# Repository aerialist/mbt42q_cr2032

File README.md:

# MDBT42Q BLE module breakout board

This is a breakout board for MDBT42Q module, a nRF52 based BLE.
https://www.seeedstudio.com/MDBT42Q-nRF52832-based-BLE-module-p-2736.html
http://www.raytac.com/product/ins.php?index_id=31

Schematics is largely copied from and inspired by Adafruit Feather nRF52 Bluefruit LE
https://www.adafruit.com/product/3406
https://learn.adafruit.com/bluefruit-nrf52-feather-learning-guide/introduction

and Redbear BLE Nano v2
https://redbear.cc/product/ble/ble-nano-2-soldered.html
https://github.com/redbear/nRF5x/tree/master/nRF52832

so that Arduino BSP developed by Adafruit or Redbear could be used as well as SDK from Nordic.
(Personally I'd recommend to go with Adafruit now that Redbear joined Particle)

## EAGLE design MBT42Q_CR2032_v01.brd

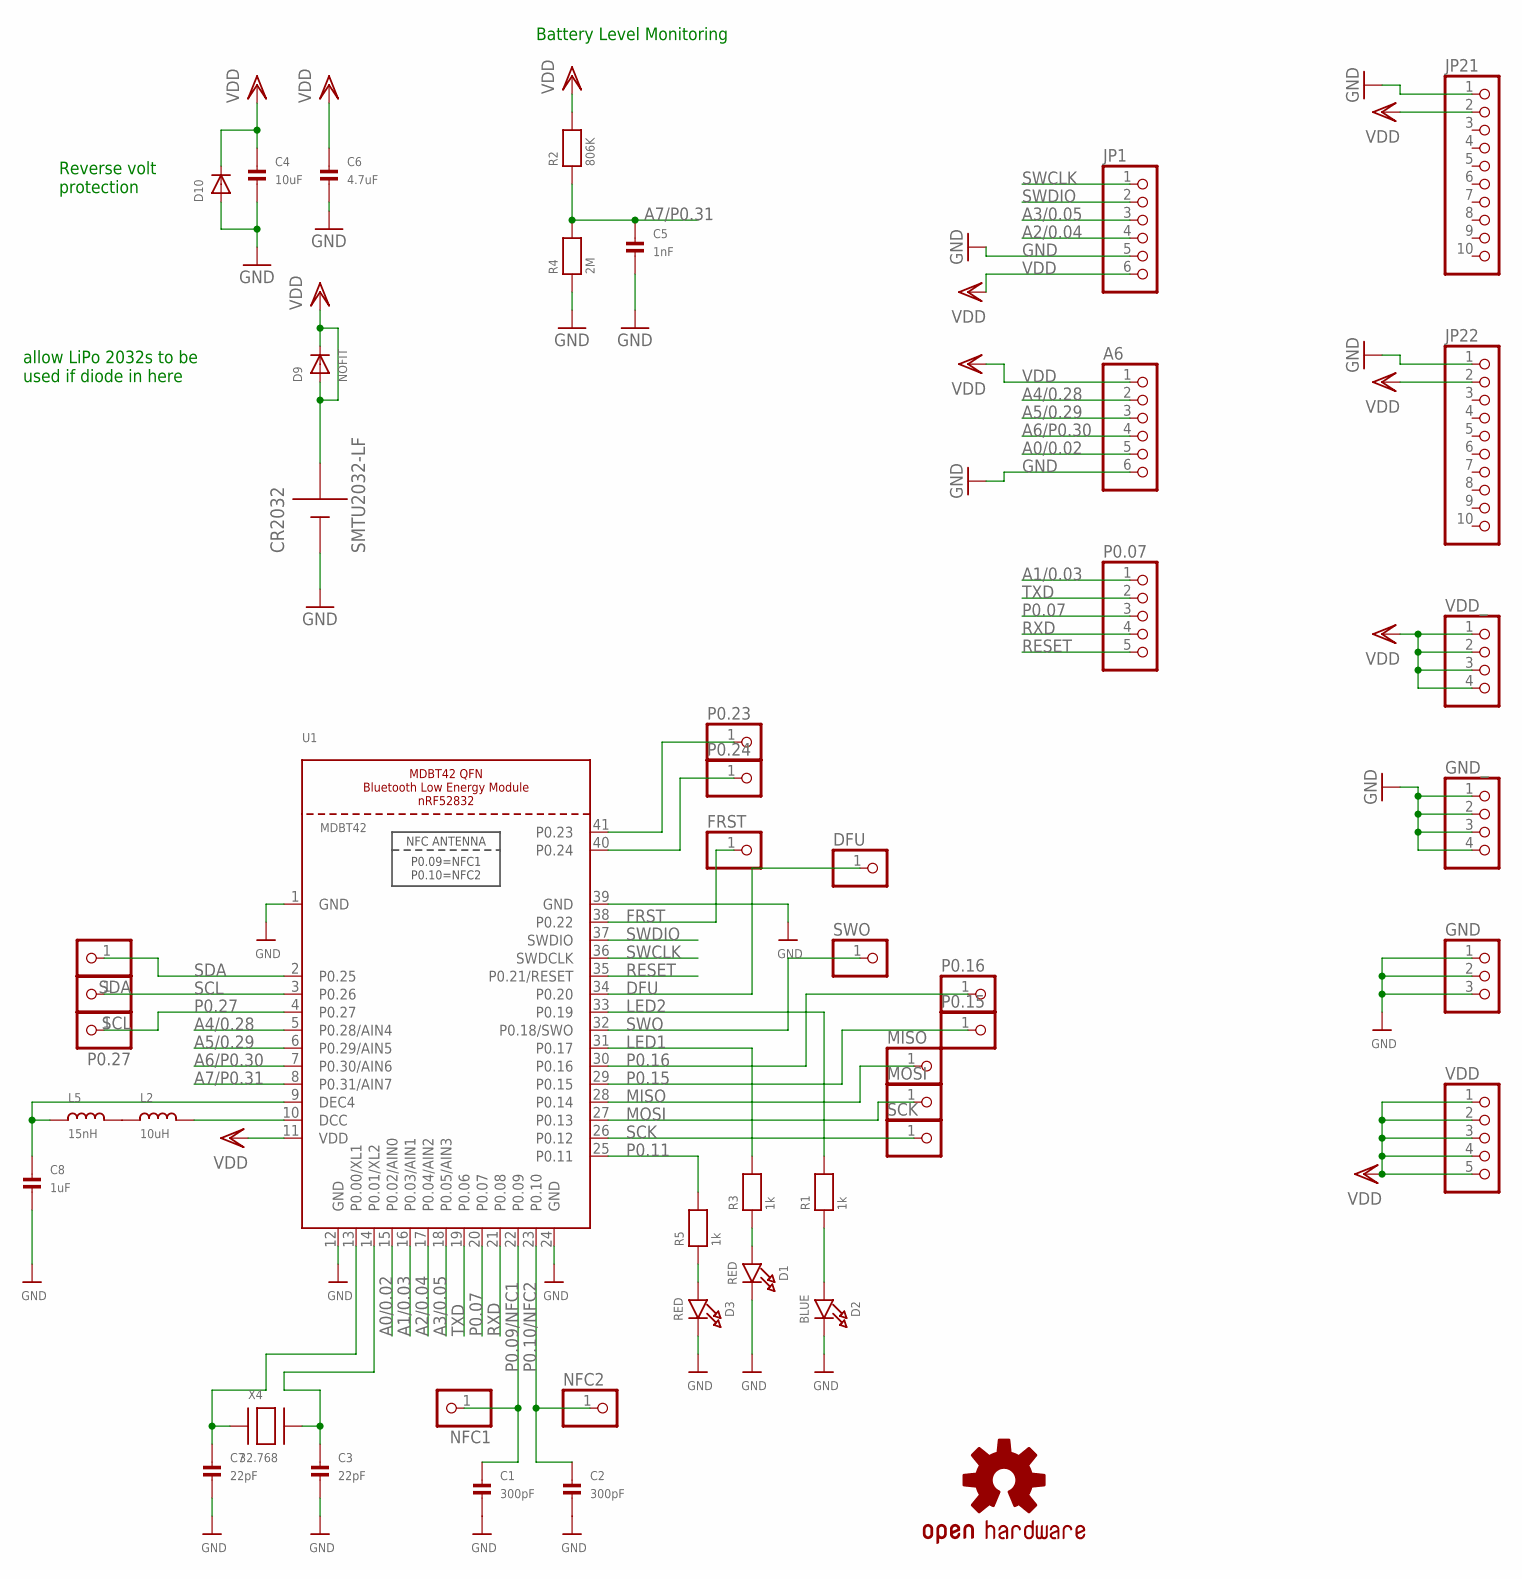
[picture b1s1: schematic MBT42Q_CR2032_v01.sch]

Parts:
A6: HEADER-1X6ROUND; 1X06_ROUND
C1, C2: 300pF; 0805
C3, C7: 22pF; 0805
C4: 10uF; 0805
C5: 1nF; 0805
C6: 4.7uF; 0805
C8: 1uF; 0805
CR2032: SMTU2032-LF
D1, D3: RED; CHIPLED_0805_NOOUTLINE
D2: BLUE; CHIPLED_0805_NOOUTLINE
D9: NOFIT; SOD-523
D10: DIODESOD-523; SOD-523
DFU: HEADER-1X1ROUND; 1X01_ROUND
FRST: HEADER-1X1ROUND; 1X01_ROUND
GND: HEADER-1X3ROUND; 1X03_ROUND
GND_: HEADER-1X4ROUND; 1X04_ROUND
JP1: HEADER-1X6ROUND; 1X06_ROUND
JP21, JP22: HEADER-1X10ROUND; 1X10_ROUND
L2: 10uH; _0805
L5: 15nH; _0805
LOGO1: OSHW-LOGOS; OSHW-LOGO-S
MISO: HEADER-1X1ROUND; 1X01_ROUND
MOSI: HEADER-1X1ROUND; 1X01_ROUND
NFC1, NFC2: HEADER-1X1ROUND; 1X01_ROUND
P0.07: HEADER-1X5ROUND; 1X05_ROUND
P0.15, P0.16, P0.23, P0.24, P0.27: HEADER-1X1ROUND; 1X01_ROUND
R1, R3, R5: 1k; 0805
R2: 806K; 0805
R4: 2M; 0805
SCK: HEADER-1X1ROUND; 1X01_ROUND
SCL: HEADER-1X1ROUND; 1X01_ROUND
SDA: HEADER-1X1ROUND; 1X01_ROUND
SWO: HEADER-1X1ROUND; 1X01_ROUND
U1: MDBT42; BLE_MODULE_RAYTAC_MDBT42
VDD: HEADER-1X5ROUND; 1X05_ROUND
VDD_: HEADER-1X4ROUND; 1X04_ROUND
X4: 32.768; XTAL3215

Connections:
A0/0.02: A6.5, U1.15 (P0.02/AIN0)
A1/0.03: P0.07.1, U1.16 (P0.03/AIN1)
A2/0.04: JP1.4, U1.17 (P0.04/AIN2)
A3/0.05: JP1.3, U1.18 (P0.05/AIN3)
A4/0.28: A6.2, U1.5 (P0.28/AIN4)
A5/0.29: A6.3, U1.6 (P0.29/AIN5)
A6/P0.30: A6.4, U1.7 (P0.30/AIN6)
A7/P0.31: C5.1, R2.1, R4.2, U1.8 (P0.31/AIN7)
DFU: DFU.1, U1.34 (P0.20)
FRST: FRST.1, U1.38 (P0.22)
GND: A6.6, C1.2, C2.2, C3.2, C4.2, C5.2, C6.2, C7.2, C8.2, CR2032.P$2 (GND), D1.C, D2.C, D3.C, D10.A, GND.1, GND.2, GND.3, GND_.1, GND_.2, GND_.3, GND_.4, JP1.5, JP21.1, JP22.1, R4.1, U1.1 (GND), U1.12 (GND), U1.24 (GND), U1.39 (GND)
LED1: R3.2, U1.31 (P0.17)
LED2: R1.2, U1.33 (P0.19)
MISO: MISO.1, U1.28 (P0.14)
MOSI: MOSI.1, U1.27 (P0.13)
unnamed: C7.1, U1.13 (P0.00/XL1), X4.P$1
unnamed: C3.1, U1.14 (P0.01/XL2), X4.P$2
unnamed: L2.2, U1.10 (DCC)
unnamed: L2.1, L5.2
unnamed: D1.A, R3.1
unnamed: D3.A, R5.1
unnamed: D2.A, R1.1
unnamed: C8.1, L5.1, U1.9 (DEC4)
unnamed: P0.24.1, U1.40 (P0.24)
unnamed: P0.23.1, U1.41 (P0.23)
P0.07: P0.07.3, U1.20 (P0.07)
P0.09/NFC1: C1.1, NFC1.1, U1.22 (P0.09)
P0.10/NFC2: C2.1, NFC2.1, U1.23 (P0.10)
P0.11: R5.2, U1.25 (P0.11)
P0.15: P0.15.1, U1.29 (P0.15)
P0.16: P0.16.1, U1.30 (P0.16)
P0.27: P0.27.1, U1.4 (P0.27)
RESET: P0.07.5, U1.35 (P0.21/RESET)
RXD: P0.07.4, U1.21 (P0.08)
SCK: SCK.1, U1.26 (P0.12)
SCL: SCL.1, U1.3 (P0.26)
SDA: SDA.1, U1.2 (P0.25)
SWCLK: JP1.1, U1.36 (SWDCLK)
SWDIO: JP1.2, U1.37 (SWDIO)
SWO: SWO.1, U1.32 (P0.18/SWO)
TXD: P0.07.2, U1.19 (P0.06)
VDD: A6.1, C4.1, C6.1, CR2032.P$1 (3V), D9.A, D9.K (C), D10.K (C), JP1.6, JP21.2, JP22.2, R2.2, U1.11 (VDD), VDD.1, VDD.2, VDD.3, VDD.4, VDD.5, VDD_.1, VDD_.2, VDD_.3, VDD_.4

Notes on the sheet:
allow LiPo 2032s to be used if diode in here
Reverse volt protection
Battery Level Monitoring

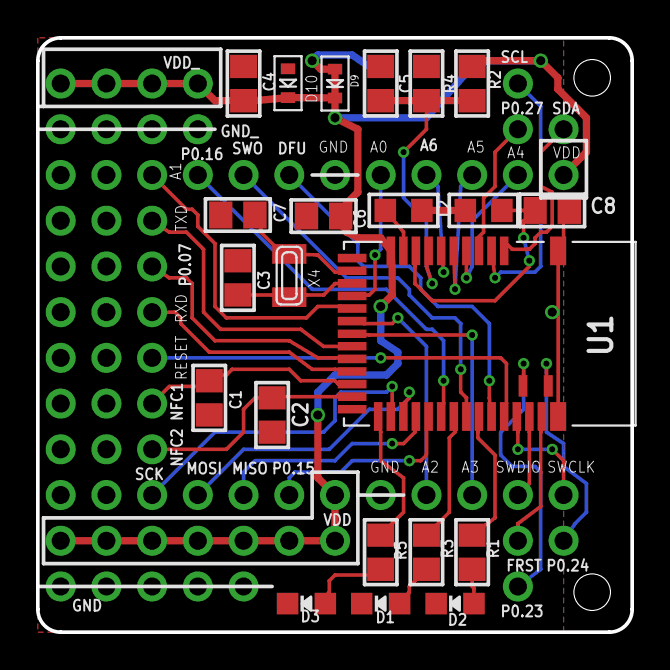
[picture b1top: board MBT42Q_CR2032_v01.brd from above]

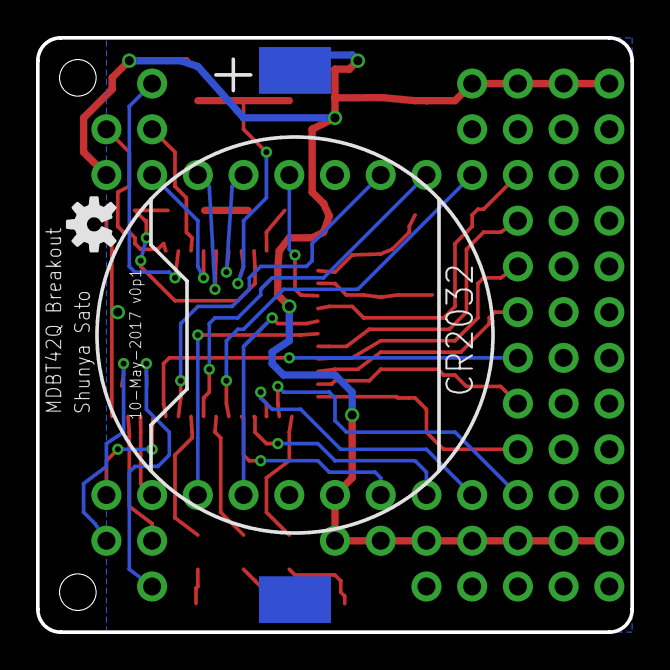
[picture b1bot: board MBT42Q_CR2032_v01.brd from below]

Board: 2 copper layers, 33.0 x 33.0 mm, 48 parts (2 on the bottom side), 42 nets.

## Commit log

2018-10-23 v01 files (garbers to order pcb is in zip)
2018-10-23 Add readme

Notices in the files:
parts and their libraries:
microbuilder: This work is placed in the public domain, and may be freely used for commercial and non-commercial work with the following conditions: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
SparkFun-Aesthetics: Licensing: Creative Commons ShareAlike 4.0 International - https://creativecommons.org/licenses/by-sa/4.0
